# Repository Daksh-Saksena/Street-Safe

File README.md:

# StreetSafe:
Disaster-response system designed to help people navigate safely during heavy rain and flooding. It improves on traditional GPS by using real-time data to guide users away from unsafe roads. Also the MAIN thing- An autonomous drone that can monitor conditions on the ground, update routes, and assist in search and rescue when situations become bad

So there are 2 parts of our Project, the physical design and drone , and the front end code base:-

___

# DRONE:
We designed the entire custom model including electronics (and 2 custom PCBS) in fusion and kicad, and made a wiring diagram including all the components and the wiring.
## What differentiates us?
Due to our goal of a helpful autonomous weatherproof drone, we had to add multiple unique differentiating parts-

1. Weatherproofing and waterproofing while maintaining airflow to cool components
2. Constant Lidar sensing on top of the drone to autonomously navigate
3. Payload mechanisms which can easilt be swapped out, For a start we have designed two mechanisms already:

* First Aid and small package deliverer - We designed a payload dropper mechanism to drop first aid boxes in times of flooded rains

* WIFI booster - In tree surrounded areas wifi connectivity gets worse exponentially so our drone acts as a network booster such that people can connect to internet and can call in case of emergencies.

___

# CODE:
This codebase is split into two main parts:
1. A Raspberry Pi 5 control system that is designed to run on actual hardware -> WARNING! ! ! -> WE DONT HAVE THE PHSYICAL COMPONENTS YET SO THIS IS LIKE A PLACEHOLDER!
2. A simulation (for testing and demoing) and dashboard system that runs in the browser and backend

Both parts implement the same core idea: an autonomous system that moves toward a goal or keep patrol while continuously avoiding obstacles and adapting to its environment.
1. Raspberry Pi (real-world system)
The pi module contains the code intended to run on a Raspberry Pi connected to a drone.
This part of the code:
* Connects to a flight controller using MAVLink
* Reads data from sensors such as LiDAR and distance sensors
* Processes that data to detect obstacles and measure distances
* Runs a control loop that decides how the drone should move
* Sends movement commandsback to the FC

In each cycle, the system:
1. Reads sensor data
2. Determines if the path ahead is clear
3. Adjusts direction if obstacles are detected
4. Continues moving toward the goal
This is the execution layer that would control a real drone.

2. Simulator + Dashboard (testing system)
The backend and frontend modules together act as a simulation environment.
This 
* Simulates the drone’s position and movement on a map
* Allows obstacles and walls to be placed interactively
* Runs the same navigation logic used on the Pi
* Displays everything visually in real time
It handles
* Routing between locations
* Flood-aware path calculation
* System state updates

The frontend:
* Displays the map (Leaflet)
* Shows the drone, its path, and obstacles
* Updates continuously as the system runs

Key ideas:--
* Move toward a goal or post etc.
* Detect obstacles
* Adjust direction dynamically
* Continue until the destination is reached
The simulator is used for testing and visualisaion (looks v cool) , while the Raspberry Pi code is designed to run the same logic on real hardware or atleast i think it will work .

## How to use:
To run: 
In bash
cd ........./streetsafe
./run_demo.sh

Then open:
http://localhost:9000

This starts the backend and launches dashboard where you can see- drone moving, place obstacles, and test navigation.

___

## Why did we do this? 
where we live-> bangalore gets heavy rains all the time (even in the summer) and its really bad traffic on top of the already infamous bangalore traffic but this can also get quite deadly, so we started this originally as a hackathon project (just some code which is now sitting in Old-website) but then we realised that this could actually be a fun and usefull project and here we are!

Note: Shipping prices are high even on the cheapest project, due to customs while shipping to where we live (India). We have selected the cheapest options.

___

## 3D MODEL

___

## WIRING DIAGRAM

___

## 3D MODEL OF ELECTRONICS

___

## PAYLOAD 1 - WiFi

___

## PAYLOAD 2 - Dropping

___

## PCB 1,2 and 3: FC, GPS and PAYLOAD

___
## Bill of Materials

| Item               | Specific Part                               | Unit Price (INR) | Quantity | Total Price (INR) | URL                                                                                                                      | Running Total |
| :----------------- | :------------------------------------------ | :--------------- | :------- | :---------------- | :----------------------------------------------------------------------------------------------------------------------- | :------------ |
| PCB Components     | Electronic Components for 3 Custom PCBs     | 9,785            | 1        | 9,785             | LCSC, Robu, DigiKey                                                                                                      | 9,785         |
| Primary LiDAR      | LDROBOT D500                                | 7,520            | 1        | 7,520             | [Link](https://robu.in/product/ldrobot-dtof-lidar-stl-19p-360-omni-directional-lidar/)                                   | 17,305        |
| Motors             | Emax ECOII 2807 1300KV                      | 1,700            | 4        | 6,800             | [Link](https://hitechxyz.in/products/emax-ecoii-2807-1300kv-brushless-motor)                                             | 24,105        |
| PCB Manufacturing  | PCB Fabrication (3 Custom PCBs)             | 5,890            | 1        | 5,890             | SEEED Fusion                                                                                                             | 29,995        |
| Battery            | 6S 4500mAh Li-ion                           | 4,100            | 1        | 4,100             | [Link](https://robu.in/product/pro-range-inr-21700-p45b-22-2v-4500mah-6s1p-35a-45a-discharge-li-ion-drone-battery-pack/) | 34,095        |
| WiFi Module        | ESP32                                       | 1,400            | 1        | 1,400             | [Link](https://robocraze.com/products/wifi-kit-32)                                                                       | 35,495        |
| Propeller          | Gemfan 7040                                 | 200              | 4        | 800               | [Link](https://hitechxyz.in/products/pro-range-propellers-7040-flash-pc-3-blade-propellers-2cw-2ccw-black)               | 36,295        |
| BEC                | 13S 5V BEC For Quad                         | 741              | 1        | 741               | [Link](https://www.flyrobo.in/yrrc-2-13s-5v-5a-bec-module)                                                               | 37,036        |
| NFC Tag            | PN532 NFC RFID Module                       | 261              | 1        | 261               | [Link](https://www.flyrobo.in/pn532-nfc-rfid-module-v3-kit)                                                              | 37,297        |
| Antenna            | 6dBi 2.4GHz 5GHz Dual Band WiFi SMA Antenna | 62               | 1        | 62                | [Link](https://robocraze.com/products/6dbi-2-4ghz-5ghz-dual-band-wifi-rp-sma-antenna-20cm-u-fl-ipex-cable)               | 37,359        |
| Companion Computer | Raspberry Pi 5 (4GB)                        | 0                | 1        | 0                 | Already Have                                                                                                             | 37,359        |
| Frame              | 3D Printed using PETG-CF (cost negligible)  | 0                | 1        | 0                 | Cost Negligible                                                                                                          | 37,359        |
| Radio              | FS-i6                                       | 0                | 1        | 0                 | Already Have                                                                                                             | 37,359        |
| ESC                | 4-in-1 ESC                                  | 0                | 1        | 0                 | Self Funded                                                                                                              | 37,359        |
| Servo              | SG90                                        | 0                | 1        | 0                 | Already Have                                                                                                             | 37,359        |
| Hot Plate          | SMD Rework Hot Plate                        | 0                | 1        | 0                 | Macondo Shop                                                                                                             | 37,359        |
| Soldering Iron     | Soldering Iron Kit                          | 0                | 1        | 0                 | Macondo Shop                                                                                                             | 37,359        |
| **Total**          |                                             |                  |          |                   |                                                                                                                          | **37,359**    |

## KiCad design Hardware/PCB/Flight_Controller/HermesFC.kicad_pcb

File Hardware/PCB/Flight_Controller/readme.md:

# Flight Controller

A flight controller <br>
Its job is to keep the drone stable <br>
its based off the hermes fc <br>

---

## Components

Its based on an STM32F405 chip. See BOM for more clarity.

---

## Assembly Instructions

Were using a stencil for assembly, as this pcb has very tightly packed components. We highly recommend this. Please know how to use a hot plate.

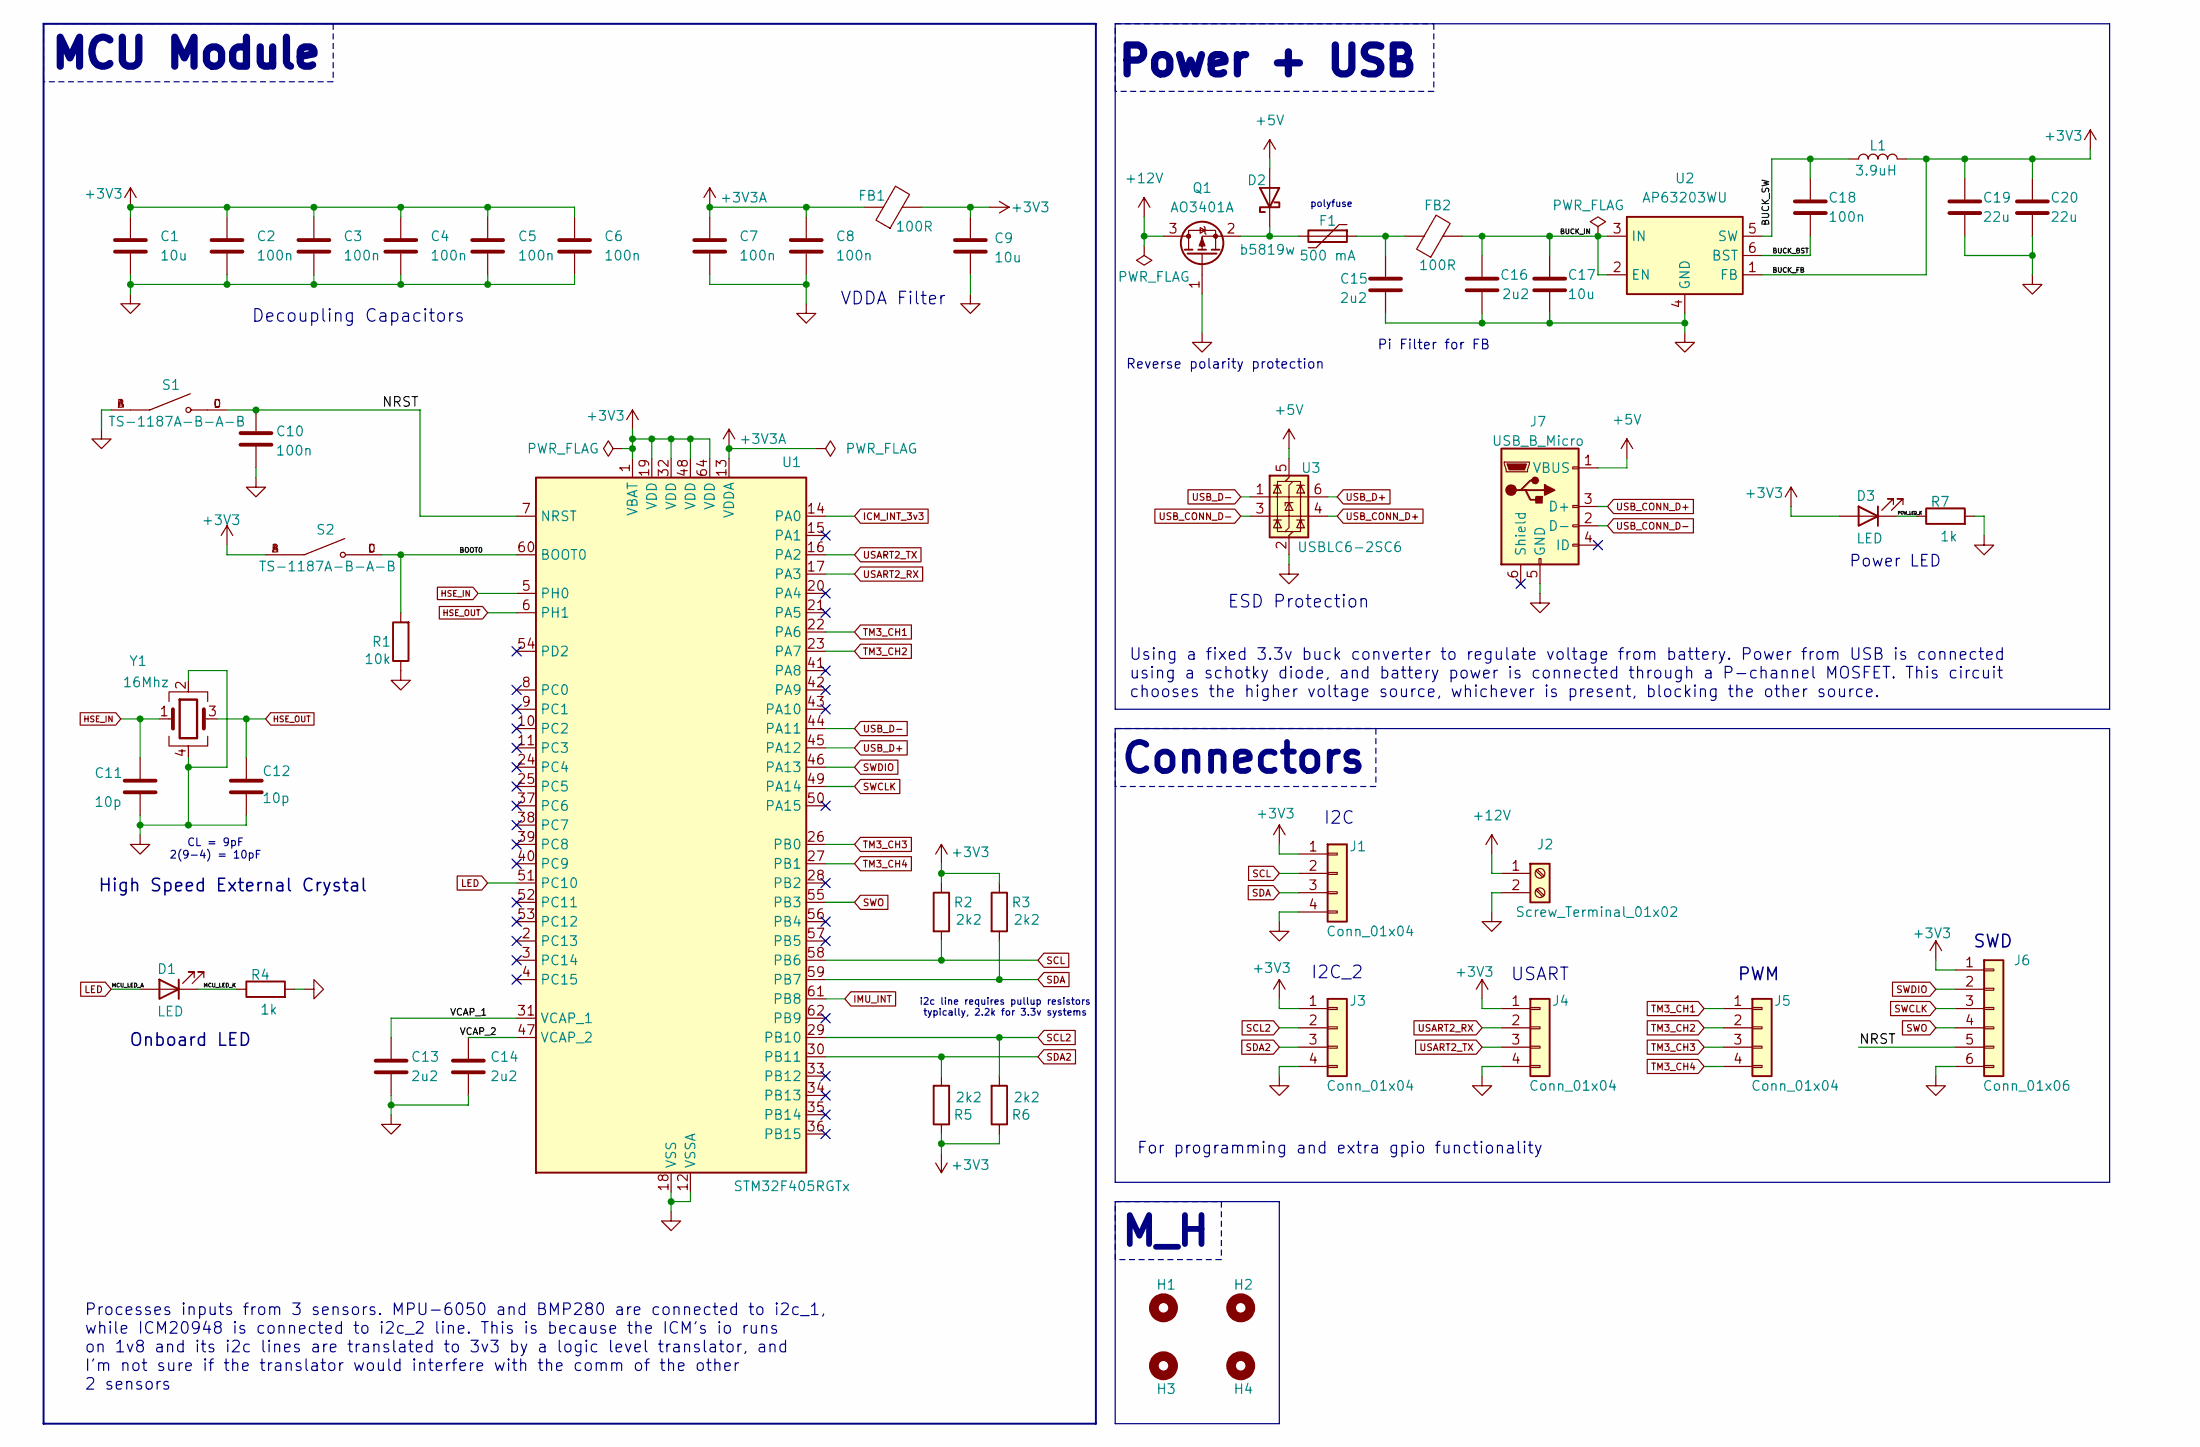
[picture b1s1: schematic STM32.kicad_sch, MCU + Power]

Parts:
C1, C9, C17: 10u; C_0603_1608Metric
C2, C3, C4, C5, C6, C7, C8, C10: 100n; C_0402_1005Metric
C11, C12: 10p; C_0603_1608Metric
C13, C14, C15, C16: 2u2; C_0603_1608Metric
C18: 100n; C_0805_2012Metric
C19, C20: 22u; C_0805_2012Metric
D1, D3: LED; LED_0603_1608Metric
D2: b5819w; D_SOD-123
F1: 500 mA; Fuse_0603_1608Metric
FB1, FB2: 100R; L_0805_2012Metric
H1, H2, H3, H4: MountingHole; MountingHole_4.3mm_M4_Pad_Via
J1, J3, J4, J5: Conn_01x04; PinSocket_1x04_P2.54mm_Vertical
J2: Screw_Terminal_01x02; TerminalBlock_Xinya_XY308-2.54-2P_1x02_P2.54mm_Horizontal
J6: Conn_01x06; PinSocket_1x06_P2.54mm_Vertical
J7: USB_B_Micro; USB_Micro-B_Amphenol_10118193-0001LF_Horizontal
L1: 3.9uH; L_Taiyo-Yuden_MD-5050
Q1: AO3401A; SOT-23
R1: 10k; R_0603_1608Metric
R2, R3, R5, R6: 2k2; R_0603_1608Metric
R4, R7: 1k; R_0603_1608Metric
S1, S2: TS-1187A-B-A-B; SW_TS-1187A-B-A-B; PARTREV A0
U1: STM32F405RGTx; LQFP-64_10x10mm_P0.5mm
U2: AP63203WU; TSOT-23-6
U3: USBLC6-2SC6; SOT-23-6
Y1: 16Mhz; Crystal_SMD_3225-4Pin_3.2x2.5mm

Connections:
+3V3: C1.1, C2.1, C3.1, C4.1, C5.1, C6.1, C9.1, C19.1, C20.1, D3.2 (A), FB1.2, J1.1, J3.1, J4.1, J6.1, L1.2, R2.1, R3.1, R5.1, R6.1, S2.A, S2.B, U1.1 (VBAT), U1.19 (VDD), U1.32 (VDD), U1.48 (VDD), U1.64 (VDD), U2.1 (FB); also elsewhere on the board
+3V3A: C7.1, C8.1, FB1.1, U1.13 (VDDA)
+5V: D2.2 (A), J7.1 (VBUS), U3.5 (VBUS)
+12V: J2.1, Q1.3 (D)
/STM32/BOOT0: R1.2, S2.C, S2.D, U1.60 (BOOT0)
/STM32/BUCK_BST: C18.2, U2.6 (BST)
/STM32/BUCK_IN: C16.1, C17.1, FB2.2, U2.2 (EN), U2.3 (IN)
/STM32/BUCK_SW: C18.1, L1.1, U2.5 (SW)
/STM32/MCU_LED_K: D1.1 (K), R4.1
/STM32/NRST: C10.1, J6.5, S1.C, S1.D, U1.7 (NRST)
/STM32/POW_LED_K: D3.1 (K), R7.1
/STM32/VCAP_1: C13.1, U1.31 (VCAP_1)
/STM32/VCAP_2: C14.1, U1.47 (VCAP_2)
GND: C1.2, C2.2, C3.2, C4.2, C5.2, C6.2, C7.2, C8.2, C9.2, C10.2, C11.2, C12.2, C13.2, C14.2, C15.2, C16.2, C17.2, C19.2, C20.2, H1.1, H2.1, H3.1, H4.1, J1.4, J2.2, J3.4, J4.4, J6.6, J7.5 (GND), Q1.1 (G), R1.1, R4.2, R7.2, S1.A, S1.B, U1.12 (VSSA), U1.18 (VSS), U1.63 (VSS), U2.4 (GND), U3.2 (GND), Y1.2, Y1.4; also elsewhere on the board
HSE_IN: C11.1, U1.5 (PH0), Y1.1
HSE_OUT: C12.1, U1.6 (PH1), Y1.3
ICM_INT_3v3: U1.14 (PA0); also elsewhere on the board
IMU_INT: U1.61 (PB8); also elsewhere on the board
LED: D1.2 (A), U1.51 (PC10)
unnamed: C15.1, F1.1, FB2.1
unnamed: D2.1 (K), F1.2, Q1.2 (S)
SCL: J1.2, R2.2, U1.58 (PB6); also elsewhere on the board
SCL2: J3.2, R6.2, U1.29 (PB10); also elsewhere on the board
SDA: J1.3, R3.2, U1.59 (PB7); also elsewhere on the board
SDA2: J3.3, R5.2, U1.30 (PB11); also elsewhere on the board
SWCLK: J6.3, U1.49 (PA14)
SWDIO: J6.2, U1.46 (PA13)
SWO: J6.4, U1.55 (PB3)
TM3_CH1: J5.1, U1.22 (PA6)
TM3_CH2: J5.2, U1.23 (PA7)
TM3_CH3: J5.3, U1.26 (PB0)
TM3_CH4: J5.4, U1.27 (PB1)
USART2_RX: J4.2, U1.17 (PA3)
USART2_TX: J4.3, U1.16 (PA2)
USB_CONN_D+: J7.3 (D+), U3.4 (I/O2)
USB_CONN_D-: J7.2 (D-), U3.3 (I/O2)
USB_D+: U1.45 (PA12), U3.6 (I/O1)
USB_D-: U1.44 (PA11), U3.1 (I/O1)

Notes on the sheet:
polyfuse
ESD Protection
Decoupling Capacitors
CL = 9pF 2(9-4) = 10pF
Using a fixed 3.3v buck converter to regulate voltage from battery. Power from USB is connected using a schotky diode, and battery power is connected through a P-channel MOSFET. This circuit chooses the higher voltage source, whichever is present, blocking the other source.
VDDA Filter
Onboard LED
i2c line requires pullup resistors typically, 2.2k for 3.3v systems
USART
Processes inputs from 3 sensors. MPU-6050 and BMP280 are connected to i2c_1, while ICM20948 is connected to i2c_2 line. This is because the ICM's io runs on 1v8 and its i2c lines are translated to 3v3 by a logic level translator, and I'm not sure if the translator would interfere with the comm of t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
M_H
Pi Filter for FB
For programming and extra gpio functionality
I2C
SWD
High Speed External Crystal
Power LED
PWM
Reverse polarity protection
MCU Module
Connectors
Power + USB
I2C_2

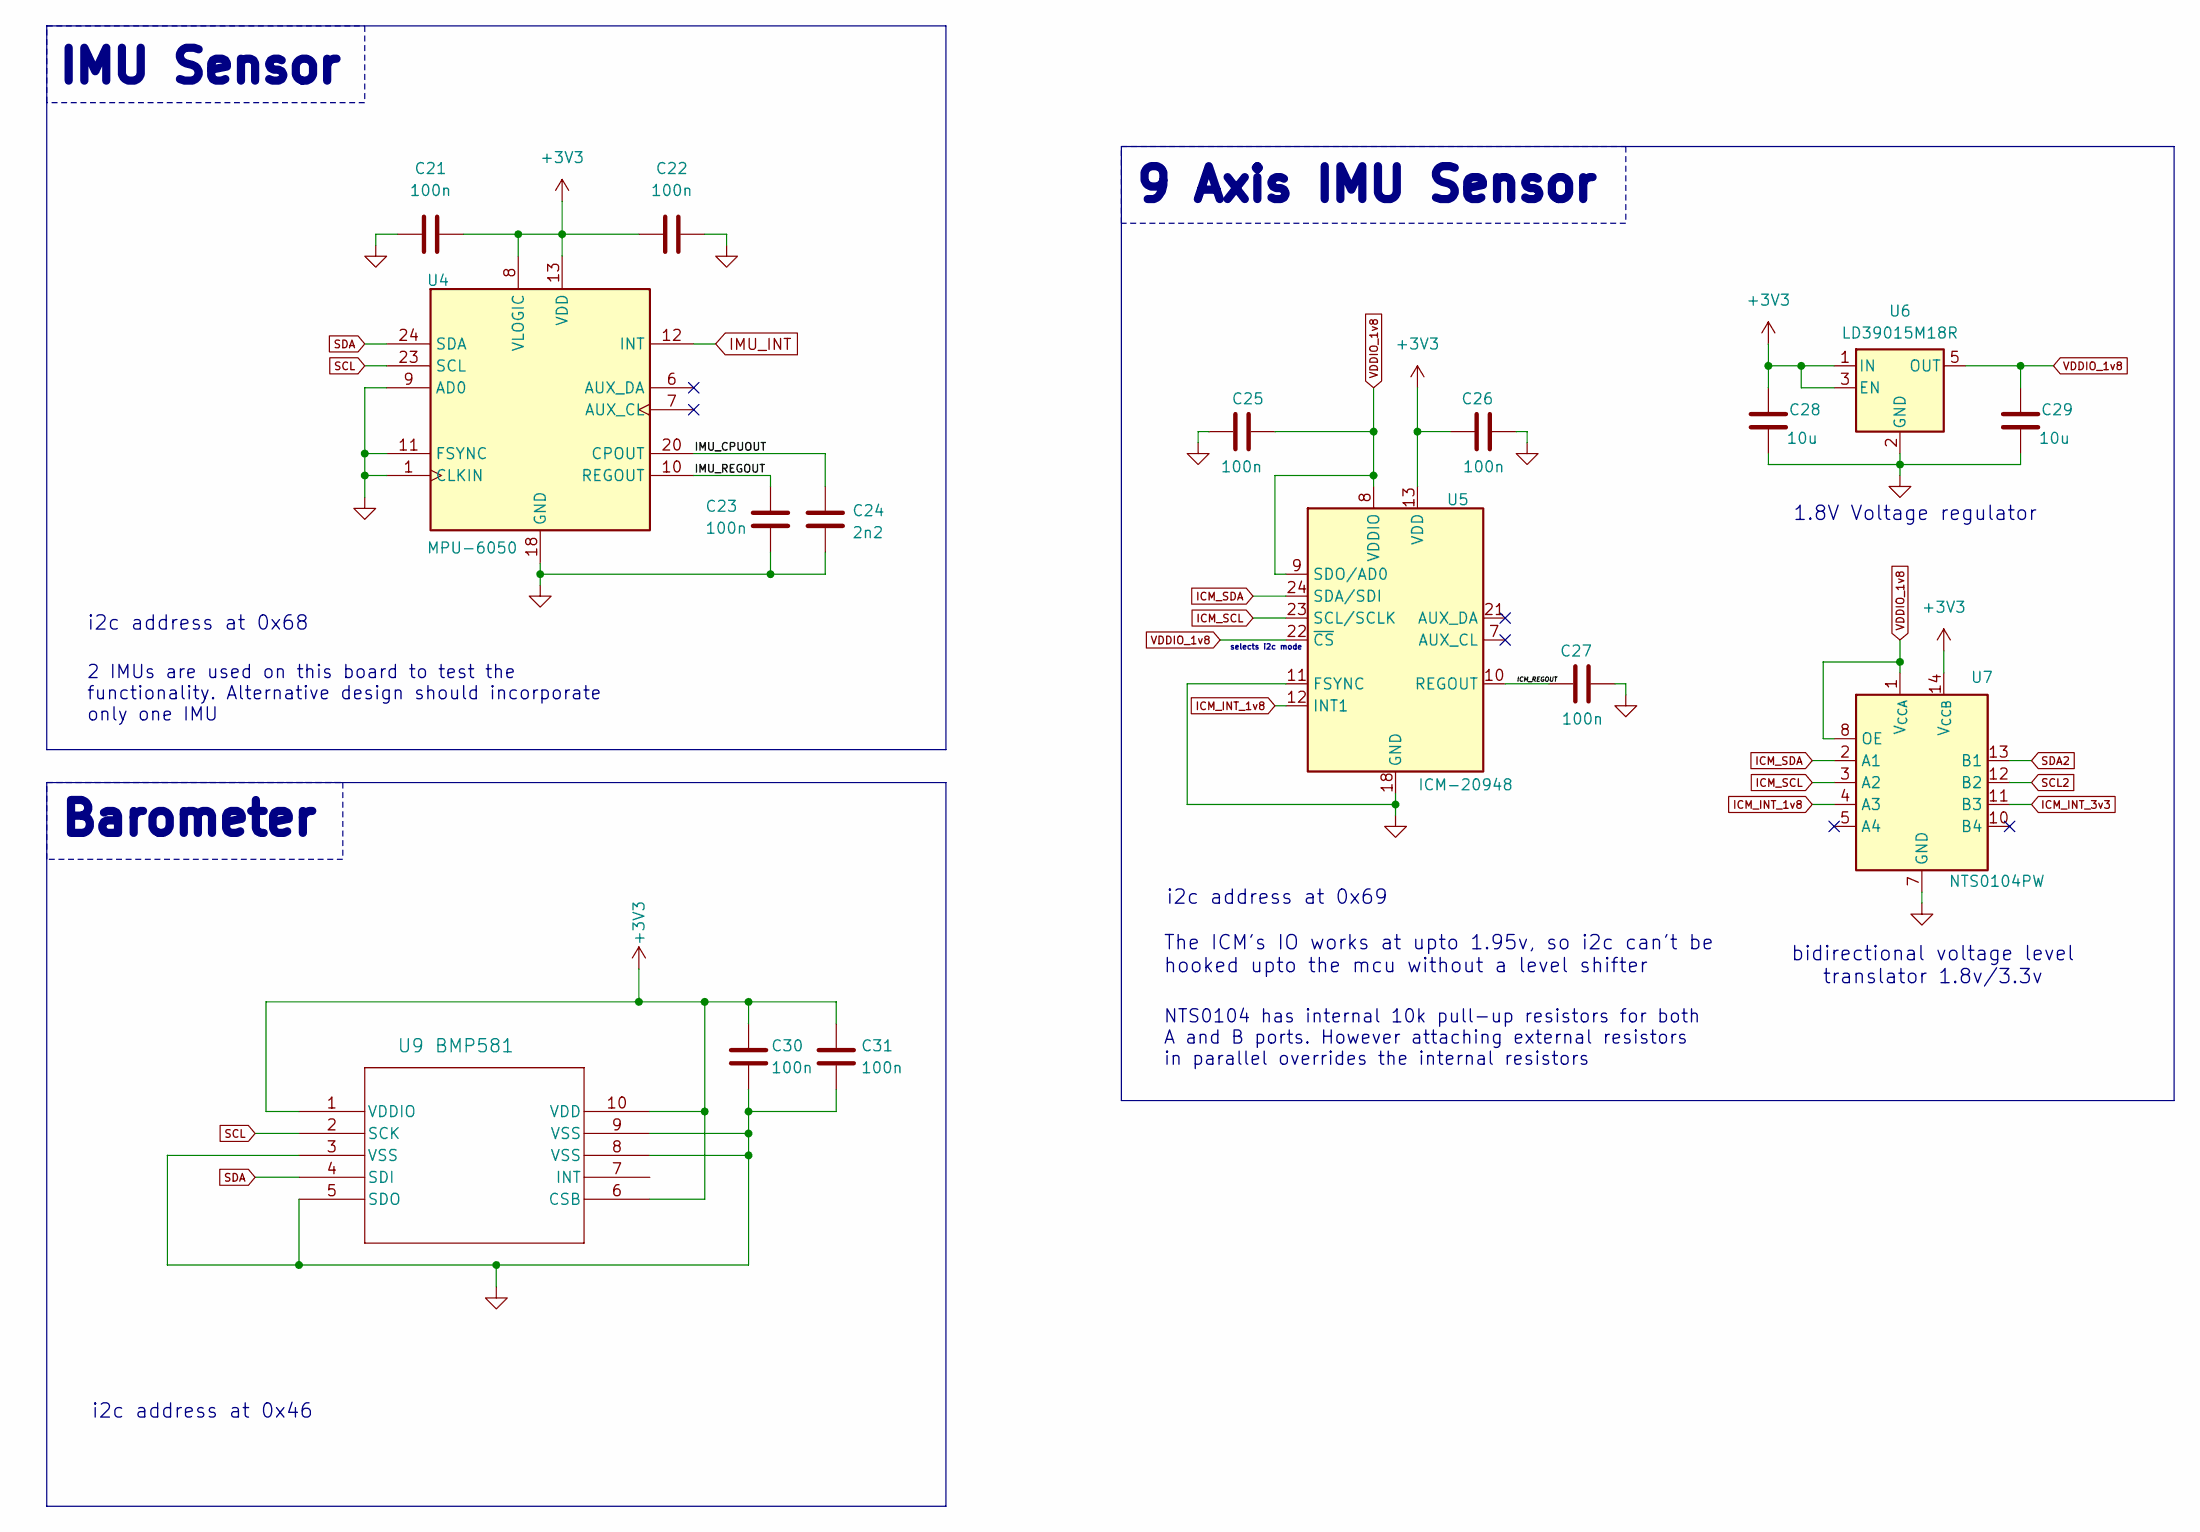
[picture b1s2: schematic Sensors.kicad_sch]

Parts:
C21, C22, C23, C25, C26, C27, C30, C31: 100n; C_0402_1005Metric
C24: 2n2; C_0603_1608Metric
C28, C29: 10u; C_0603_1608Metric
U4: MPU-6050; InvenSense_QFN-24_4x4mm_P0.5mm
U5: ICM-20948; InvenSense_QFN-24_3x3mm_P0.4mm
U6: LD39015M18R; SOT-23-5
U7: NTS0104PW; TSSOP-14_4.4x5mm_P0.65mm
U9: BMP581; QFN10_BMP581_BOS

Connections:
+3V3: C21.2, C22.1, C26.1, C28.1, C30.1, C31.2, U4.8 (VLOGIC), U4.13 (VDD), U5.13 (VDD), U6.1 (IN), U6.3 (EN), U7.14 (V_{CCB}), U9.1 (VDDIO), U9.6 (CSB), U9.10 (VDD); also elsewhere on the board
/Sensors/ICM_REGOUT: C27.1, U5.10 (REGOUT)
/Sensors/IMU_CPUOUT: C24.1, U4.20 (CPOUT)
/Sensors/IMU_REGOUT: C23.1, U4.10 (REGOUT)
GND: C21.1, C22.2, C23.2, C24.2, C25.2, C26.2, C27.2, C28.2, C29.2, C30.2, C31.1, U4.1 (CLKIN), U4.9 (AD0), U4.11 (FSYNC), U4.18 (GND), U5.11 (FSYNC), U5.18 (GND), U5.20 (GND), U6.2 (GND), U7.7 (GND), U9.3 (VSS), U9.5 (SDO), U9.8 (VSS), U9.9 (VSS); also elsewhere on the board
ICM_INT_1v8: U5.12 (INT1), U7.4 (A3)
ICM_INT_3v3: U7.11 (B3); also elsewhere on the board
ICM_SCL: U5.23 (SCL/SCLK), U7.3 (A2)
ICM_SDA: U5.24 (SDA/SDI), U7.2 (A1)
IMU_INT: U4.12 (INT); also elsewhere on the board
SCL: U4.23 (SCL), U9.2 (SCK); also elsewhere on the board
SCL2: U7.12 (B2); also elsewhere on the board
SDA: U4.24 (SDA), U9.4 (SDI); also elsewhere on the board
SDA2: U7.13 (B1); also elsewhere on the board
VDDIO_1v8: C25.1, C29.1, U5.8 (VDDIO), U5.9 (SDO/AD0), U5.22 (~CS), U6.5 (OUT), U7.1 (V_{CCA}), U7.8 (OE)

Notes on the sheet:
9 Axis IMU Sensor
i2c address at 0x46
1.8V Voltage regulator
2 IMUs are used on this board to test the functionality. Alternative design should incorporate only one IMU
NTS0104 has internal 10k pull-up resistors for both A and B ports. However attaching external resistors in parallel overrides the internal resistors
IMU Sensor
i2c address at 0x69
Barometer
i2c address at 0x68
selects i2c mode
bidirectional voltage level translator 1.8v/3.3v
The ICM's IO works at upto 1.95v, so i2c can't be hooked upto the mcu without a level shifter

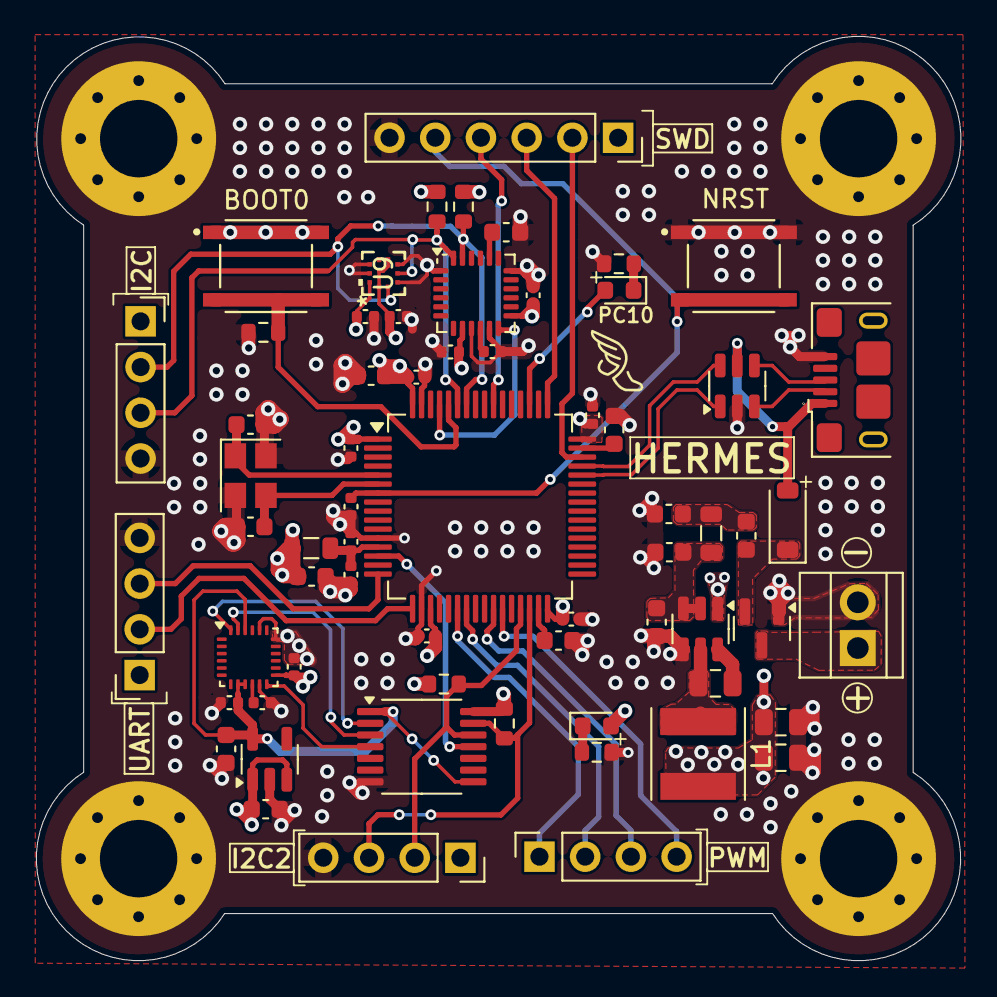
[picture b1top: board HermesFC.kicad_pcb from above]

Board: 4 copper layers, 51.4 x 51.3 mm, 68 parts (0 on the bottom side), 45 nets.

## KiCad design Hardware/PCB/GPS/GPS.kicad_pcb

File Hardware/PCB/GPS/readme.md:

# GPS PCB

Sooo this is the gps pcb, we made it ourselves in kicad. 

---

## Function
Accurate gps to provide the mission software real time GPS locations to an accuracy of about 1.5m. It also has a compass to tell the software where the drone is pointed.

---

## Components
So the raw GPS module is the uBlox SAM m10q.  
The compass is the IST 8310 module.  
*See bom for more clarity.*

---

We added all the production files in the production folder. I tried to add as many file types as possible so that anyone who needs it can get it easily.

--- 

# Assembly Instructions
1.  **Solder Paste Application:** It is highly recommended to use a laser-cut stainless steel **solder stencil** rather than manual hand-pasting to prevent solder bridging across close-proximity components.
2.  **Component Placement:** Carefully place the surface-mount devices (SMDs), taking extra care with the orientation of the SAM-M10Q patch antenna and the IST8310 alignment dot.
3.  **Reflow Method:** Utilize a temperature-controlled SMD hotplate or reflow oven for assembly. If you are new to hotplate soldering, review proper thermal profiling guidelines to avoid overheating the sensitive internal RF shielding of the GPS receiver.

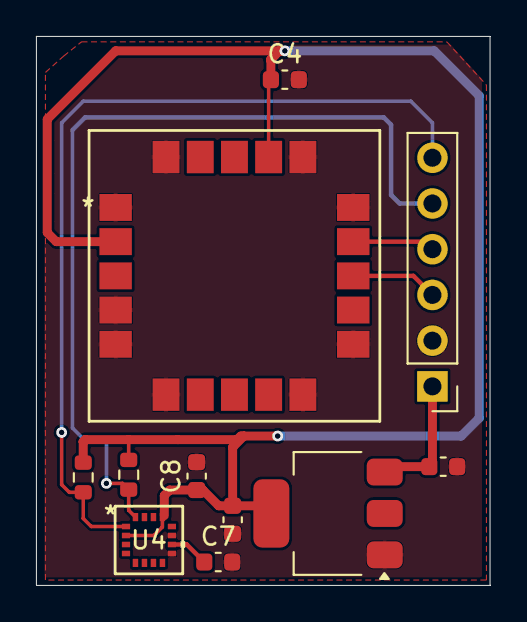
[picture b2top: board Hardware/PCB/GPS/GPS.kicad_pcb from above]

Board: 2 copper layers, 25.2 x 30.5 mm, 11 parts (0 on the bottom side), 8 nets.

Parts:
C1: 10uF; C_0603_1608Metric
C2: 22uF; C_0603_1608Metric
C4: 100nF; C_0603_1608Metric
C7: 10uf; C_0603_1608Metric
C8: 1 uf; C_0603_1608Metric
J1: Conn_01x06_Socket; PinHeader_1x06_P2.54mm_Vertical
R1, R2: 4.7kΩ; R_0603_1608Metric
U1: SAM-M10Q-00B; SAM-M10Q_UBL
U2: AMS1117-3.3; SOT-223-3_TabPin2
U4: MMC5983MA; MMC5983MA_MEM

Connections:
3v3: C2.1, C4.1, C8.1, R1.1, R2.1, U1.2 (V_IO), U1.17 (VCC), U2.2 (VO), U4.2 (VDD), U4.4 (SPI_CS), U4.13 (VDDIO)
/+5v: C1.1, J1.1, U2.3 (VI)
/comp_scl: J1.6, R2.2, U4.1 (SCL/SPI_SCK)
/comp_sda: J1.5, R1.2, U4.16 (SDA/SPI_SDI)
/gps_rxd: J1.4, U1.14 (RXD)
/gps_txd: J1.3, U1.13 (TXD)
unnamed: C7.1, U4.10 (CAP)
gnd: C1.2, C2.2, C4.2, C7.2, C8.2, J1.2, U1.1 (GND), U1.4 (GND), U1.5 (GND), U1.6 (GND), U1.10 (GND), U1.11 (GND), U1.15 (GND), U1.16 (GND), U1.20 (GND), U2.1 (GND), U4.9 (GND), U4.11 (GND)

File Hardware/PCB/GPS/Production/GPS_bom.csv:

"Id";"Designator";"Footprint";"Quantity";"Designation";"Supplier and ref";
1;"C1";"C_0603_1608Metric";1;"10uF";;;
2;"C2";"C_0603_1608Metric";1;"22uF";;;
3;"C4";"C_0603_1608Metric";1;"100nF";;;
4;"C7";"C_0603_1608Metric";1;"10uf";;;
5;"C8";"C_0603_1608Metric";1;"1 uf";;;
6;"J1";"PinHeader_1x06_P2.54mm_Vertical";1;"Conn_01x06_Socket";;;
7;"R1, R2";"R_0603_1608Metric";2;"4.7kΩ";;;
8;"U1";"SAM-M10Q_UBL";1;"SAM-M10Q-00B";;;
9;"U2";"SOT-223-3_TabPin2";1;"AMS1117-3.3";;;
10;"U4";"MMC5983MA_MEM";1;"MMC5983MA";;;

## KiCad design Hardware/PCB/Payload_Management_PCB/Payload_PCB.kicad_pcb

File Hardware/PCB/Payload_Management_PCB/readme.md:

# Payload Management PCB

This is an esp-32 based management pcb, we made it ourselves in kicad.

---

## Function
This PCB is designed to do 3 things:
* **a) Detect which payload is connected via nfc**
* **b) Provide power to the payload** (has a mosfet to start/stop power when needed)
* **c) Help the PI5:** It basically is designed to offload micro tasks from the pi5, so the pi5 can focus on object avoidance. It handles NFC module identification, manages power routing, and filters raw sensor data before passing clean data to the pi5.

---

## Components
It uses an ESP32 S3 MINI 1U as the microcontroller.  
*See BOM for more clarity.*

---

We added all the production files in the production folder. 

---

## Assembly Instructions
Were using stencils since its our first time working with pcbs. This pcb contains tightly packed components, so we recommend this aswell. Please refer to youtube tutorials aswell.

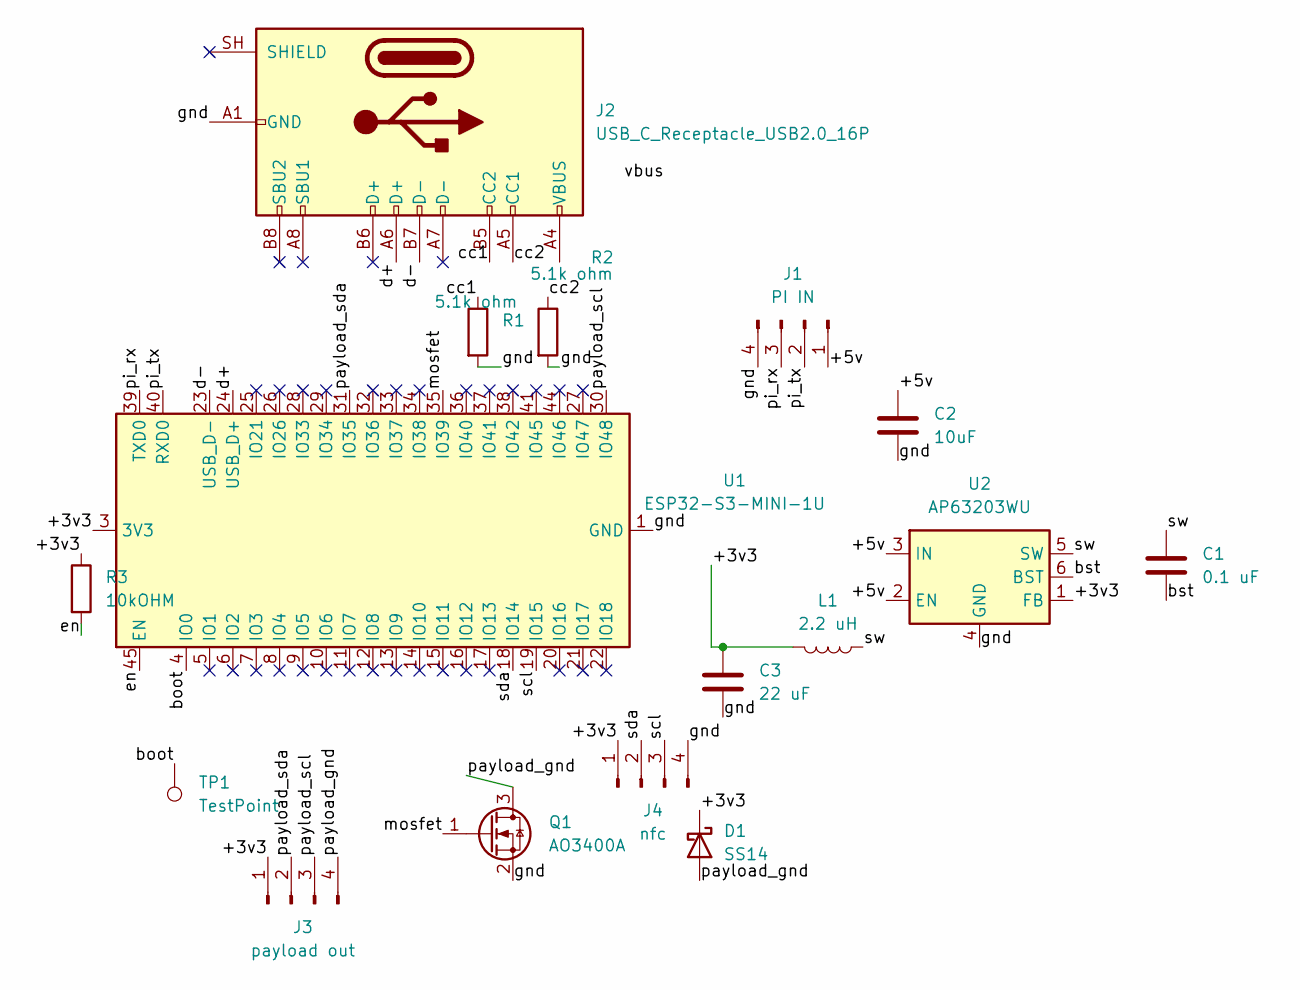
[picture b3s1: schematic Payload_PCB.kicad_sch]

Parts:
C1: 0.1 uF; C_0603_1608Metric
C2: 10uF; C_0603_1608Metric
C3: 22 uF; C_0603_1608Metric
D1: SS14; D_SMA
J1: PI IN; PinHeader_1x04_P2.54mm_Vertical
J2: USB_C_Receptacle_USB2.0_16P; USB_C_Receptacle_GCT_USB4105-xx-A_16P_TopMnt_Horizontal
J3: payload out; PinHeader_1x04_P2.54mm_Vertical
J4: nfc; PinHeader_1x04_P2.54mm_Vertical
L1: 2.2 uH; L_1008_2520Metric
Q1: AO3400A; SOT-23
R1, R2: 5.1k ohm; R_0603_1608Metric
R3: 10kOHM; R_0603_1608Metric
TP1: TestPoint; TestPoint_Pad_D1.0mm
U1: ESP32-S3-MINI-1U; ESP32-S2-MINI-1U
U2: AP63203WU; TSOT-23-6

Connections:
/+3v3: C3.1, D1.1 (K), J3.1, J4.1, L1.2, R3.1, U1.3 (3V3), U2.1 (FB)
/+5v: C2.1, J1.1, U2.2 (EN), U2.3 (IN)
/boot: TP1.1 (1_1), U1.4 (IO0)
/bst: C1.2, U2.6 (BST)
/cc1: J2.B5 (CC2), R1.1
/cc2: J2.A5 (CC1), R2.1
/d+: J2.A6 (D+), U1.24 (USB_D+)
/d-: J2.B7 (D-), U1.23 (USB_D-)
/en: R3.2, U1.45 (EN)
/gnd: C2.2, C3.2, J1.4, J2.A1 (GND), J2.A12 (GND), J2.B1 (GND), J2.B12 (GND), J4.4, Q1.2 (S), R1.2, R2.2, U1.1 (GND), U1.2 (GND), U1.42 (GND), U1.43 (GND), U1.46 (GND), U1.47 (GND), U1.48 (GND), U1.49 (GND), U1.50 (GND), U1.51 (GND), U1.52 (GND), U1.53 (GND), U1.54 (GND), U1.55 (GND), U1.56 (GND), U1.57 (GND), U1.58 (GND), U1.59 (GND), U1.60 (GND), U1.61 (GND), U1.62 (GND), U1.63 (GND), U1.64 (GND), U1.65 (GND), U2.4 (GND)
/mosfet: Q1.1 (G), U1.35 (IO39)
/payload_gnd: D1.2 (A), J3.4, Q1.3 (D)
/payload_scl: J3.3, U1.30 (IO48)
/payload_sda: J3.2, U1.31 (IO35)
/pi_rx: J1.3, U1.39 (TXD0)
/pi_tx: J1.2, U1.40 (RXD0)
/scl: J4.3, U1.19 (IO15)
/sda: J4.2, U1.18 (IO14)
/sw: C1.1, L1.1, U2.5 (SW)
unnamed: J2.A4 (VBUS), J2.A9 (VBUS), J2.B4 (VBUS), J2.B9 (VBUS)

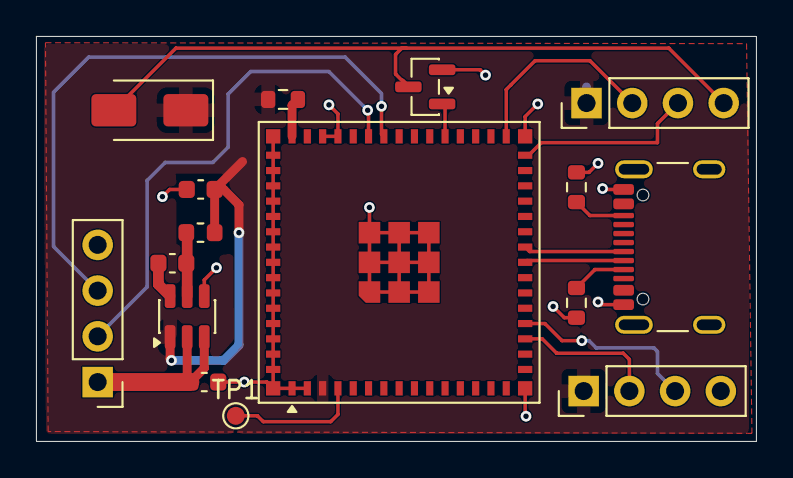
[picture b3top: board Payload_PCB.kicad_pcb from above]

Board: 2 copper layers, 40.0 x 22.5 mm, 16 parts (0 on the bottom side), 20 nets.

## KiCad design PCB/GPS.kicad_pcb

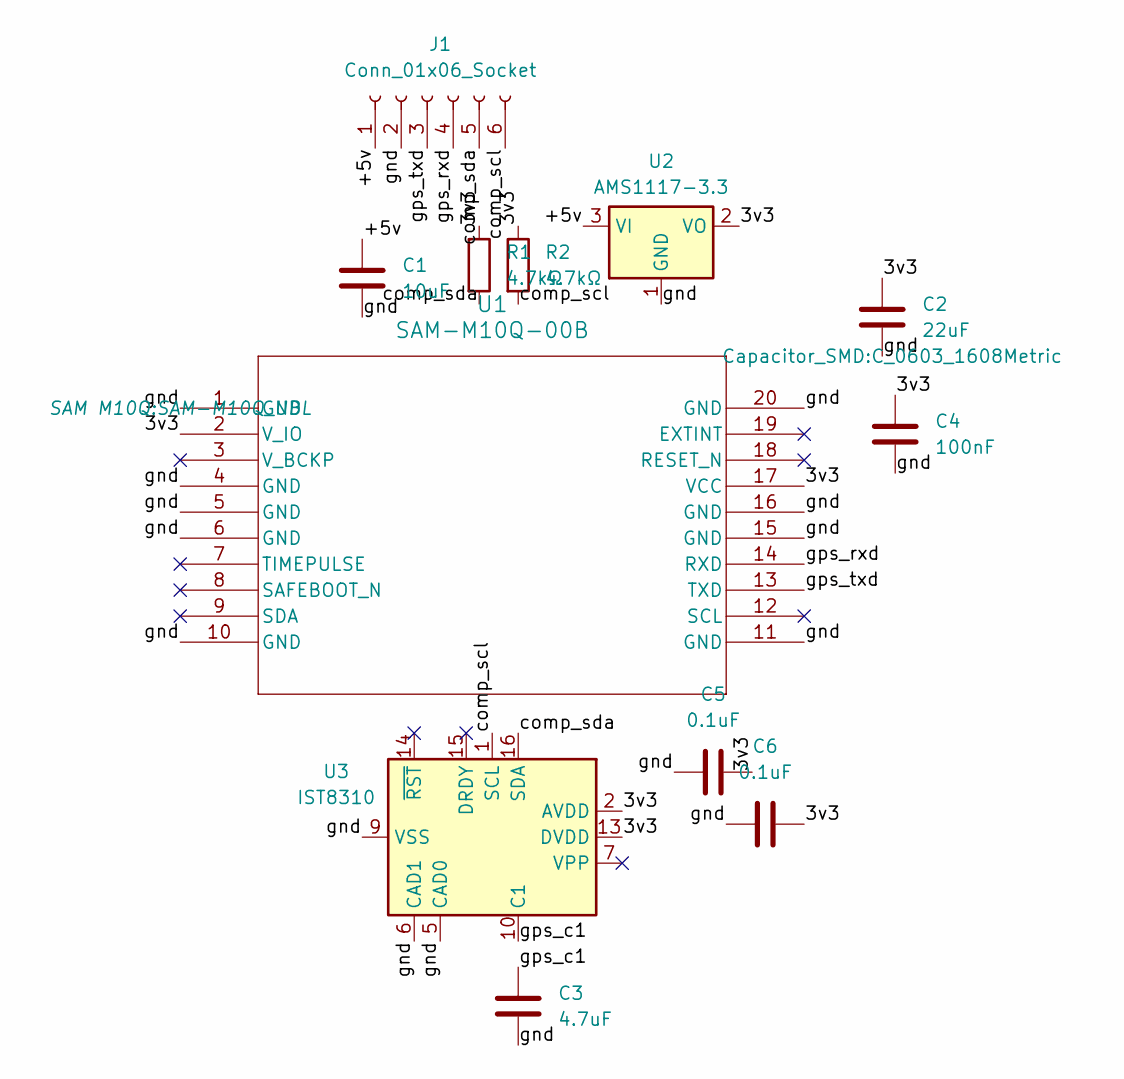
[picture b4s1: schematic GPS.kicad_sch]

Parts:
C1: 10uF; C_0603_1608Metric
C2: 22uF; C_0603_1608Metric
C3: 4.7uF; C_0603_1608Metric
C4: 100nF; C_0603_1608Metric
C5, C6: 0.1uF; C_0603_1608Metric
J1: Conn_01x06_Socket; PinHeader_1x06_P2.54mm_Vertical
R1, R2: 4.7kΩ; R_0603_1608Metric
U1: SAM-M10Q-00B; SAM-M10Q_UBL
U2: AMS1117-3.3; SOT-223-3_TabPin2
U3: IST8310; LGA-16_3x3mm_P0.5mm

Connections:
/3v3: C2.1, C4.1, C5.2, C6.2, R1.1, R2.1, U1.2 (V_IO), U1.17 (VCC), U2.2 (VO), U3.2 (AVDD), U3.13 (DVDD)
/+5v: C1.1, J1.1, U2.3 (VI)
/comp_scl: J1.6, R2.2, U3.1 (SCL)
/comp_sda: J1.5, R1.2, U3.16 (SDA)
/gnd: C1.2, C2.2, C3.2, C4.2, C5.1, C6.1, J1.2, U1.1 (GND), U1.4 (GND), U1.5 (GND), U1.6 (GND), U1.10 (GND), U1.11 (GND), U1.15 (GND), U1.16 (GND), U1.20 (GND), U2.1 (GND), U3.5 (CAD0), U3.6 (CAD1), U3.9 (VSS), U3.11 (VSS)
/gps_c1: C3.1, U3.10 (C1)
/gps_rxd: J1.4, U1.14 (RXD)
/gps_txd: J1.3, U1.13 (TXD)

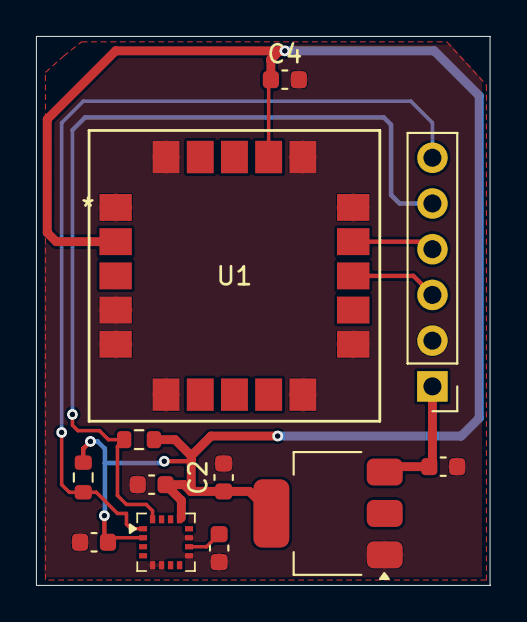
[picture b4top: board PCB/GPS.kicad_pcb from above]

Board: 2 copper layers, 25.2 x 30.5 mm, 12 parts (0 on the bottom side), 8 nets.

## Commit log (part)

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2026-03-30 Added intel-igence project into subfolder
2026-03-30 your message
2026-03-31 Added 3d models to repository
    Added completed 3d models to the repository, they include main frame, electronics shelf, water resistant cover, landing gear and everything combined in one file.
2026-03-31 read me update
2026-03-31 Initial plan
2026-03-31 Added BOM
    Added the Bill of materials as per the format.
    Note: Some items may be out of stock since as this is the end of the month, their stocks usually deplete. They usually restock within 1-2 weeks. Since we are in India, we are reliant on only a few su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
2026-04-01 read me fixing
2026-04-01 editssss
2026-04-01 small tiny update
2026-04-20 configured
2026-04-30 changes to BOM
2026-05-04 wiring diagram update
2026-05-04 readme upd
    Updated wiring diagram image reference in README.
2026-05-04 Rename Wiring Diagram.png to Wiring-Diagram.png
2026-05-04 Update README with project details and drone features
    Expanded project description and details about the drone and codebase.
2026-05-04 Update README to enhance project description
    Emphasize project name and clarify project purpose.
2026-05-04 Enhance README with project details and structure
    Expanded project description and details about the drone and codebase.
2026-05-04 Rename 3D model.png to 3D-model.png
2026-05-04 Fix image filename for Dropping payload section
2026-05-04 Create ...
2026-05-04 Create q
2026-06-03 Final BOM Updates
2026-06-03 Update PCB section to include GPS and PCB 3
2026-06-03 Rename WhatsApp Image 2026-06-03 at 9.00.57 PM.jpeg to GPS.jpeg
2026-06-09 Create placeholder
2026-06-09 renaming
2026-06-09 Update README
    Added a note about shipping prices due to customs in India.
2026-06-09 cleaned up repo
2026-06-10 cLEANED
2026-06-11 Cleaned repository
2026-06-11 Create step
2026-06-11 Create s
2026-06-11 added step files
2026-06-11 Add MIT License to the project
2026-06-11 Moved
2026-06-28 add BOM
2026-06-28 added assembly
